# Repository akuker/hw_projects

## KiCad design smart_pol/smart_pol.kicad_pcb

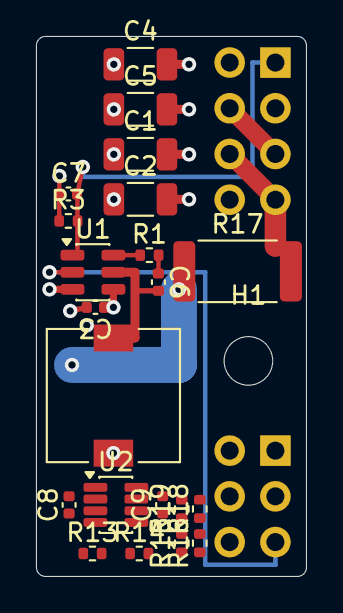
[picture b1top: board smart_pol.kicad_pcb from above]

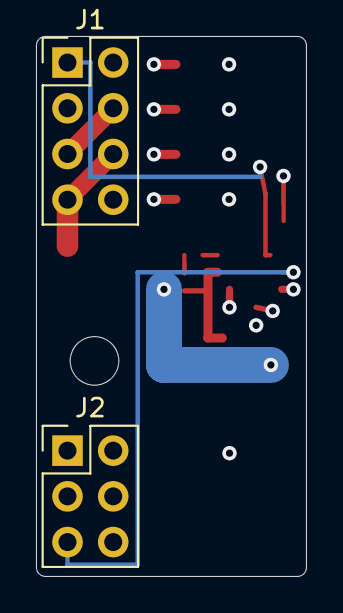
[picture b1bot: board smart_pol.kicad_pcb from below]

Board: 4 copper layers, 15.0 x 30.0 mm, 24 parts (2 on the bottom side), 16 nets.

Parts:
C1, C2: 10uF 50V; C_1206_3216Metric
C3, C6, C8, C9: 100nF; C_0402_1005Metric
C4, C5: 22uF 25V; C_1206_3216Metric
C7: 22pF; C_0402_1005Metric
H1: MountingHole; MountingHole_2.7mm_M2.5
J1: Power 2x4; PinHeader_2x04_P2.54mm_Vertical
J2: Logic 2x3; PinHeader_2x03_P2.54mm_Vertical
L1: 2.2uH 10A; L_7.3x7.3_H3.5
R1, R13, R14: 10R; R_0402_1005Metric
R3: 22k; R_0402_1005Metric
R15, R16: 4.7k; R_0402_1005Metric
R17: 10mR 2W; R_2512_6332Metric
R18, R19: 100k; R_0402_1005Metric
U1: ETA8156FT2G; SOT-23-6
U2: INA219AIDCNR; SOT-23-8

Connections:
ADDR0: J2.3, R19.1, U2.7 (A0)
ADDR1: J2.4, R18.1, U2.8 (A1)
EN: J2.5, U1.2 (EN)
FB: C7.2, J1.1, R3.2, U1.1 (FB)
GND: C1.2, C2.2, C3.2, C4.2, C5.2, C9.2, J1.2, J1.3, J1.8, R18.2, R19.2, U1.3 (GND), U2.3 (GND)
IN_M: C8.2, R14.2, U2.2 (IN-)
IN_P: C8.1, R13.2, U2.1 (IN+)
unnamed: C6.1, R1.2
unnamed: R1.1, U1.6 (BST)
unnamed: C6.2, L1.1, U1.5 (SW)
SCL: J2.2, R15.2, U2.5 (SCL)
SDA: J2.1, R16.2, U2.6 (SDA)
VBUCK: C4.1, C5.1, C7.1, L1.2, R3.1, R13.1, R17.1
VCC_IO: C9.1, J2.6, R15.1, R16.1, U2.4 (VS)
VIN: C1.1, C2.1, C3.1, J1.4, J1.5, U1.4 (IN)
VOUT: J1.6, J1.7, R14.1, R17.2

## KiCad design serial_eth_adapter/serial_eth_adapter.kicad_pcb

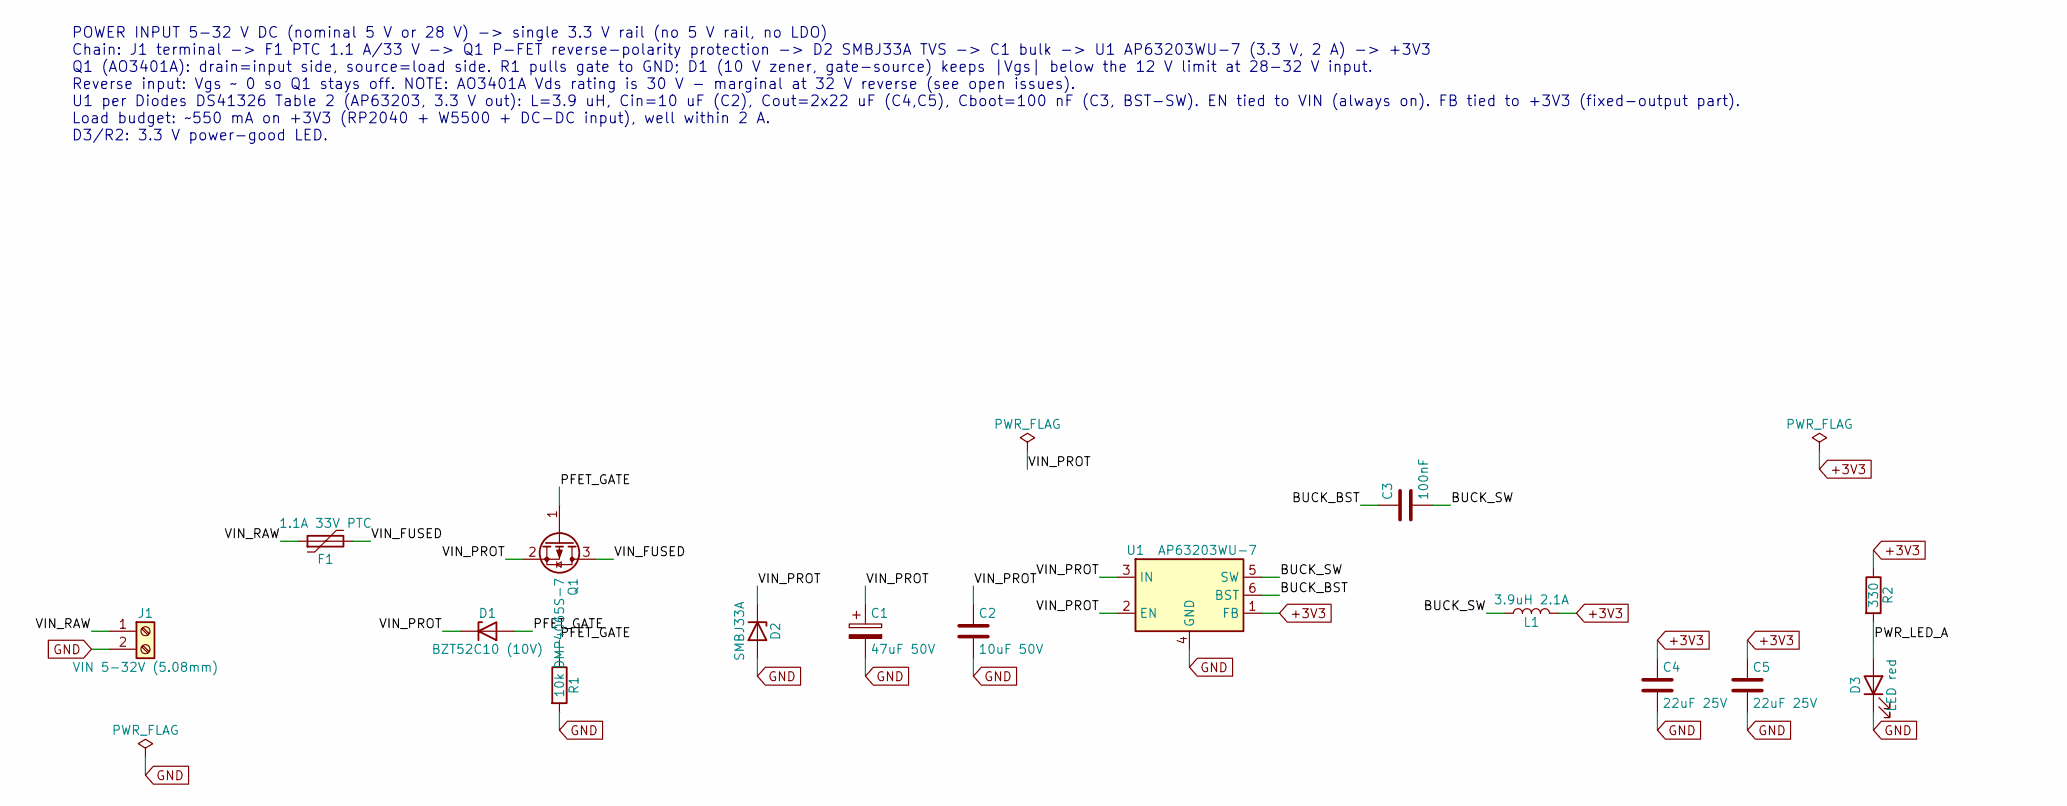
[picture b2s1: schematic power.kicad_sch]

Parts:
C1: 47uF 50V; CP_Elec_6.3x7.7; MPN RVT1H470M0607; LCSC C3349
C2: 10uF 50V; C_1206_3216Metric; MPN CL31A106KBHNNNE; LCSC C13585
C3: 100nF; C_0603_1608Metric; MPN CC0603KRX7R9BB104; LCSC C14663
C4, C5: 22uF 25V; C_0805_2012Metric; MPN CL21A226MAQNNNE; LCSC C45783
D1: BZT52C10 (10V); D_SOD-123; MPN BZT52C10; LCSC C2103
D2: SMBJ33A; D_SMB; MPN SMBJ33A; LCSC C173526
D3: LED red; LED_0603_1608Metric; MPN KT-0603R; LCSC C2286
F1: 1.1A 33V PTC; Fuse_1812_4532Metric; MPN 1812L110/33MR; LCSC C142747
J1: VIN 5-32V (5.08mm); PhoenixContact_MSTBA_2,5_2-G-5,08_1x02_P5.08mm_Horizontal; MPN KF2EDGR-5.08-2P; LCSC C441204
L1: 3.9uH 2.1A; L_Sunlord_SWPA4030S; MPN SWPA4030S3R9MT; LCSC C96899
Q1: DMP4065S-7; SOT-23; MPN DMP4065S-7; LCSC C182476
R1: 10k; R_0603_1608Metric; MPN 0603WAF1002T5E; LCSC C25804
R2: 330; R_0603_1608Metric; MPN 0603WAF3300T5E; LCSC C23138
U1: AP63203WU-7; TSOT-23-6; MPN AP63203WU-7; LCSC C780769

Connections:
+3V3: C4.1, C5.1, L1.2, R2.1, U1.1 (FB); also elsewhere on the board
/Power/BUCK_BST: C3.1, U1.6 (BST)
/Power/BUCK_SW: C3.2, L1.1, U1.5 (SW)
/Power/PFET_GATE: D1.2 (A), Q1.1 (G), R1.1
/Power/PWR_LED_A: D3.2 (A), R2.2
/Power/VIN_FUSED: F1.2, Q1.3 (D)
/Power/VIN_PROT: C1.1, C2.1, D1.1 (K), D2.1 (K), Q1.2 (S), U1.2 (EN), U1.3 (IN)
/Power/VIN_RAW: F1.1, J1.1
GND: C1.2, C2.2, C4.2, C5.2, D2.2 (A), D3.1 (K), J1.2, R1.2, U1.4 (GND); also elsewhere on the board

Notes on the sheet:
POWER INPUT 5-32 V DC (nominal 5 V or 28 V) -> single 3.3 V rail (no 5 V rail, no LDO) Chain: J1 terminal -> F1 PTC 1.1 A/33 V -> Q1 P-FET reverse-polarity protection -> D2 SMBJ33A TVS -> C1 bulk -> U1 AP63203WU-7 (3.3 V, 2 A) -> +3V3 Q1 (AO3401A): drain=input side, source=load side. R1 pulls gate 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

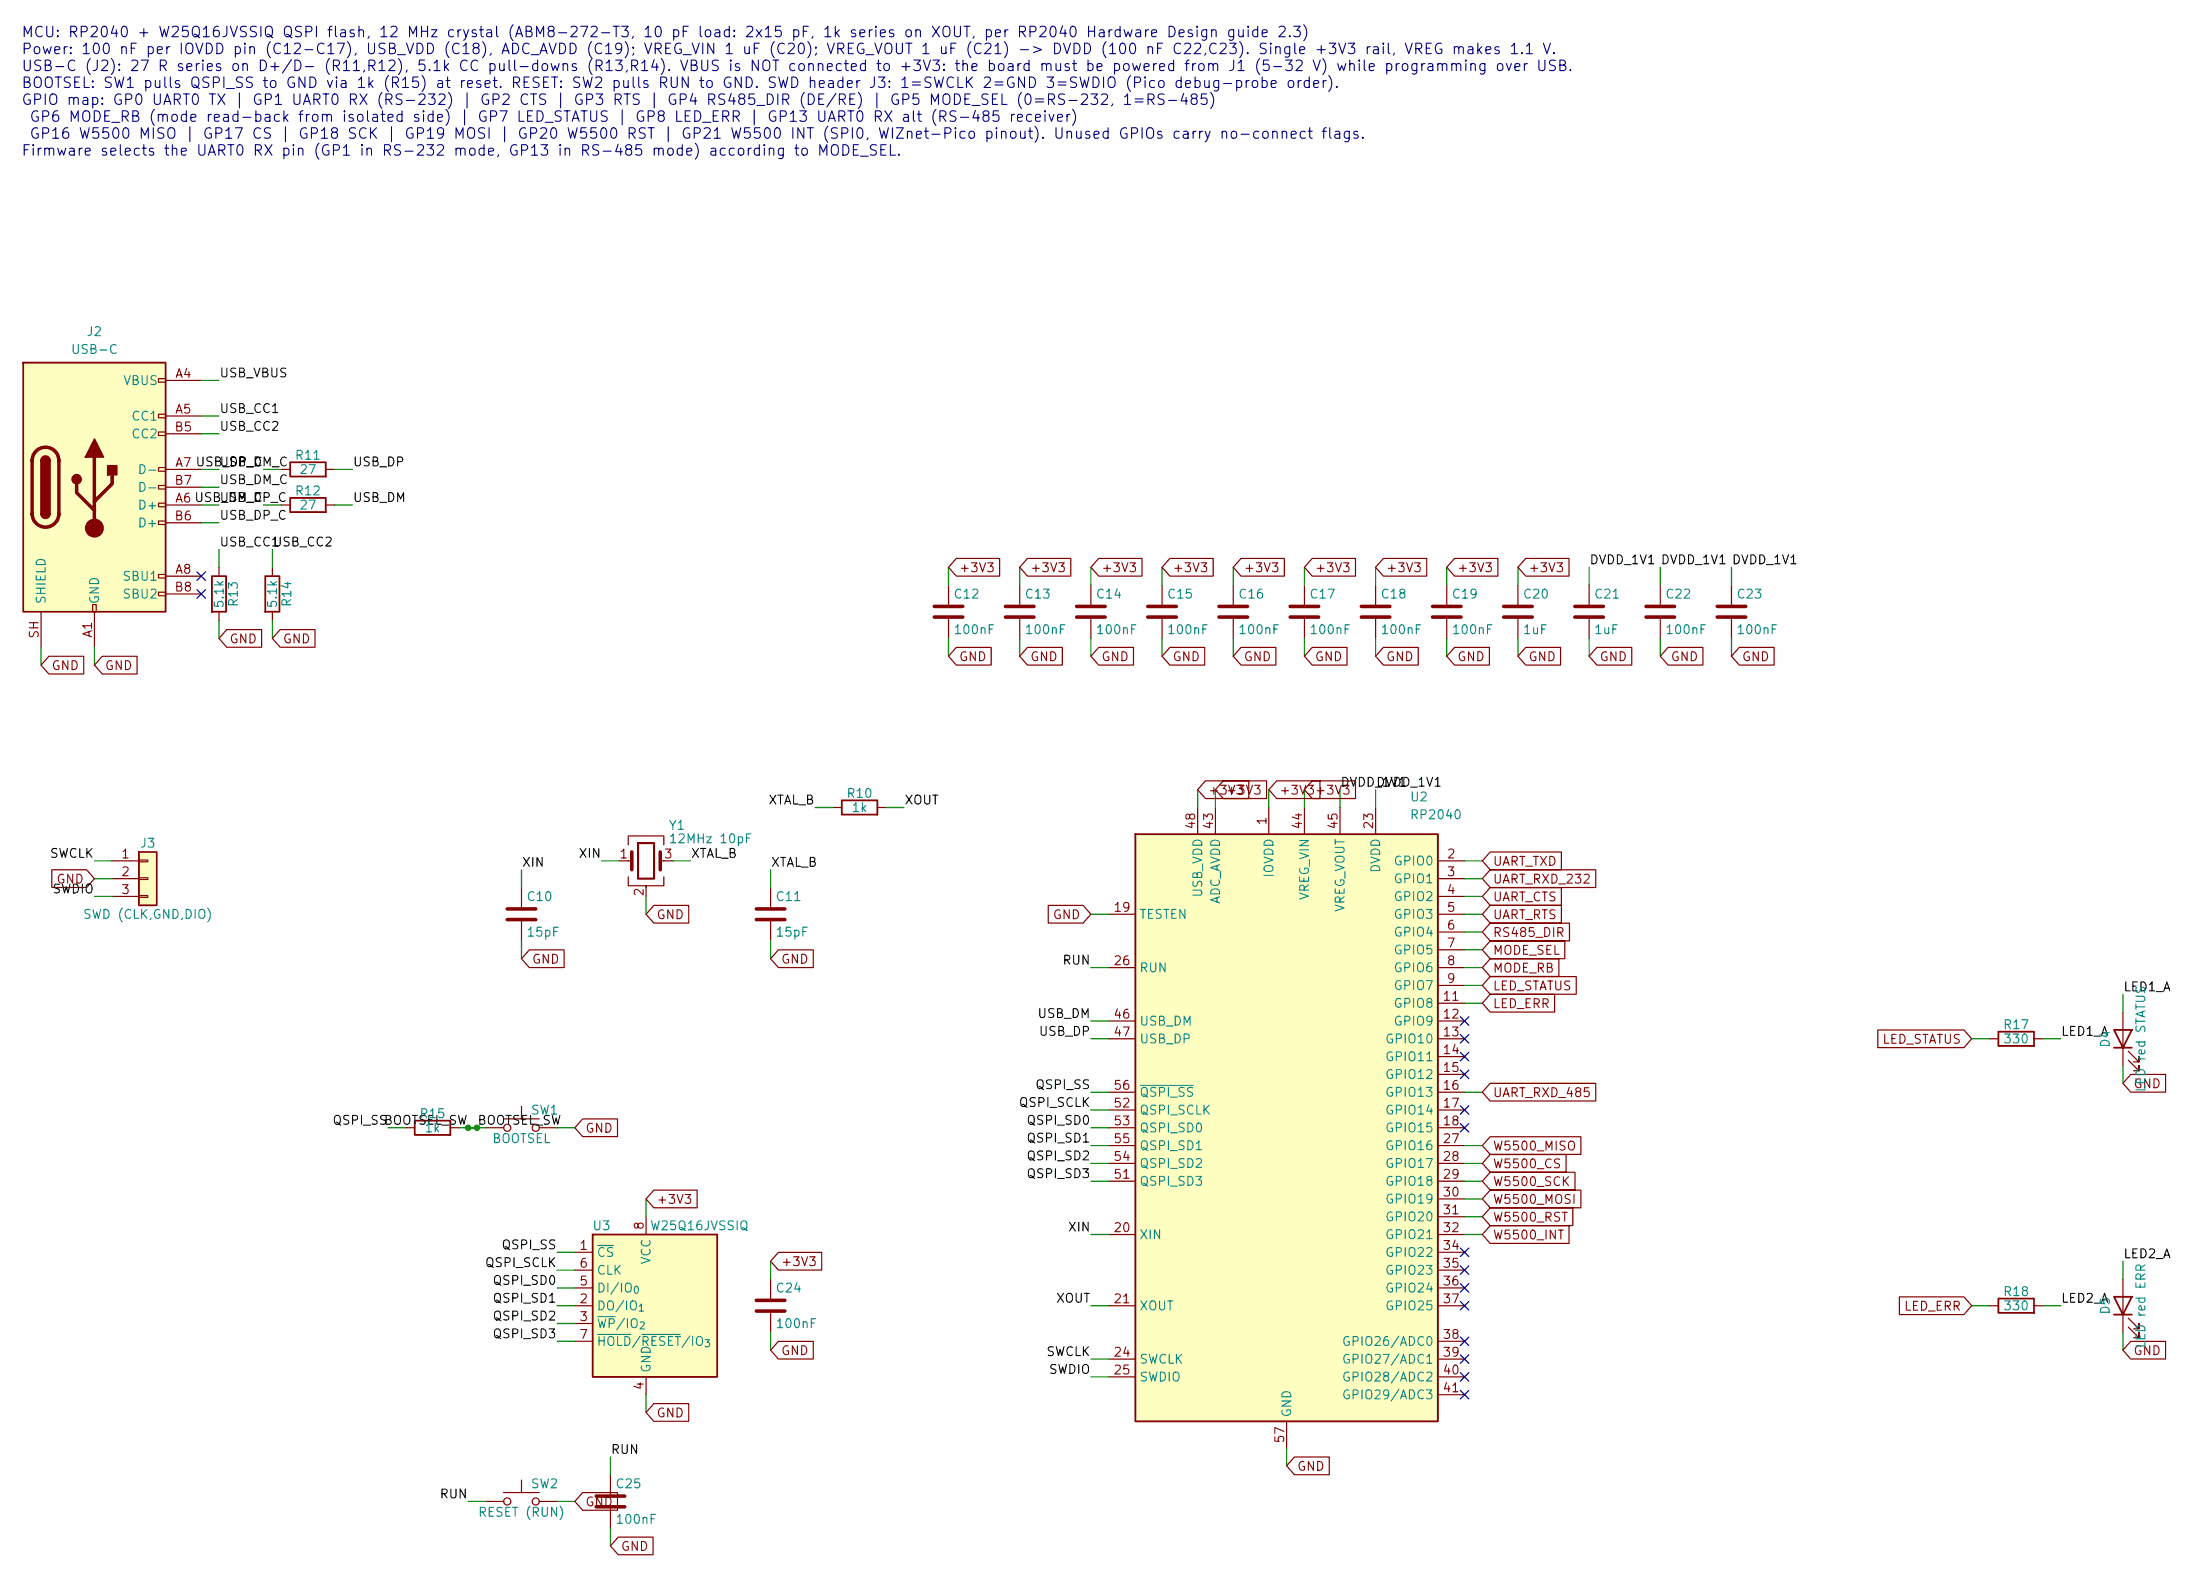
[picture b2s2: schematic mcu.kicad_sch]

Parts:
C10, C11: 15pF; C_0603_1608Metric; MPN CL10C150JB8NNNC; LCSC C1644
C12, C13, C14, C15, C16, C17, C18, C19, C22, C23, C24, C25: 100nF; C_0603_1608Metric; MPN CC0603KRX7R9BB104; LCSC C14663
C20, C21: 1uF; C_0603_1608Metric; MPN CL10A105KB8NNNC; LCSC C15849
D4: LED red STATUS; LED_0603_1608Metric; MPN KT-0603R; LCSC C2286
D5: LED red ERR; LED_0603_1608Metric; MPN KT-0603R; LCSC C2286
J2: USB-C; USB_C_Receptacle_HRO_TYPE-C-31-M-12; MPN TYPE-C-31-M-12; LCSC C165948
J3: SWD (CLK,GND,DIO); PinHeader_1x03_P2.54mm_Vertical; MPN 254PZ-1x3P-V; LCSC C53055673
R10, R15: 1k; R_0603_1608Metric; MPN 0603WAF1001T5E; LCSC C21190
R11, R12: 27; R_0603_1608Metric; MPN 0603WAF270JT5E; LCSC C25190
R13, R14: 5.1k; R_0603_1608Metric; MPN 0603WAF5101T5E; LCSC C23186
R17, R18: 330; R_0603_1608Metric; MPN 0603WAF3300T5E; LCSC C23138
SW1: BOOTSEL; SW_TS-1187A_5.1x5.1mm; MPN TS-1187A-B-A-B; LCSC C318884
SW2: RESET (RUN); SW_TS-1187A_5.1x5.1mm; MPN TS-1187A-B-A-B; LCSC C318884
U2: RP2040; QFN-56-1EP_7x7mm_P0.4mm_EP3.2x3.2mm; MPN RP2040; LCSC C2040
U3: W25Q16JVSSIQ; SOIC-8_5.3x5.3mm_P1.27mm; MPN W25Q16JVSSIQ; LCSC C82317
Y1: 12MHz 10pF; Crystal_SMD_3225-4Pin_3.2x2.5mm; MPN ABM8-272-T3; LCSC C20625731

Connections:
+3V3: C12.1, C13.1, C14.1, C15.1, C16.1, C17.1, C18.1, C19.1, C20.1, C24.1, U2.1 (IOVDD), U2.10 (IOVDD), U2.22 (IOVDD), U2.33 (IOVDD), U2.42 (IOVDD), U2.43 (ADC_AVDD), U2.44 (VREG_VIN), U2.48 (USB_VDD), U2.49 (IOVDD), U3.8 (VCC); also elsewhere on the board
/MCU/BOOTSEL_SW: R15.2, SW1.1
/MCU/DVDD_1V1: C21.1, C22.1, C23.1, U2.23 (DVDD), U2.45 (VREG_VOUT), U2.50 (DVDD)
/MCU/LED1_A: D4.2 (A), R17.2
/MCU/LED2_A: D5.2 (A), R18.2
/MCU/QSPI_SCLK: U2.52 (QSPI_SCLK), U3.6 (CLK)
/MCU/QSPI_SD0: U2.53 (QSPI_SD0), U3.5 (DI/IO_{0})
/MCU/QSPI_SD1: U2.55 (QSPI_SD1), U3.2 (DO/IO_{1})
/MCU/QSPI_SD2: U2.54 (QSPI_SD2), U3.3 (~WP/IO_{2})
/MCU/QSPI_SD3: U2.51 (QSPI_SD3), U3.7 (~HOLD/~RESET/IO_{3})
/MCU/QSPI_SS: R15.1, U2.56 (~QSPI_SS), U3.1 (~CS)
/MCU/RUN: C25.1, SW2.1, U2.26 (RUN)
/MCU/SWCLK: J3.1, U2.24 (SWCLK)
/MCU/SWDIO: J3.3, U2.25 (SWDIO)
/MCU/USB_CC1: J2.A5 (CC1), R13.1
/MCU/USB_CC2: J2.B5 (CC2), R14.1
/MCU/USB_DM: R12.2, U2.46 (USB_DM)
/MCU/USB_DM_C: J2.A7 (D-), J2.B7 (D-), R12.1
/MCU/USB_DP: R11.2, U2.47 (USB_DP)
/MCU/USB_DP_C: J2.A6 (D+), J2.B6 (D+), R11.1
/MCU/USB_VBUS: J2.A4 (VBUS), J2.A9 (VBUS), J2.B4 (VBUS), J2.B9 (VBUS)
/MCU/XIN: C10.1, U2.20 (XIN), Y1.1
/MCU/XOUT: R10.2, U2.21 (XOUT)
/MCU/XTAL_B: C11.1, R10.1, Y1.3
GND: C10.2, C11.2, C12.2, C13.2, C14.2, C15.2, C16.2, C17.2, C18.2, C19.2, C20.2, C21.2, C22.2, C23.2, C24.2, C25.2, D4.1 (K), D5.1 (K), J2.A1 (GND), J2.A12 (GND), J2.B1 (GND), J2.B12 (GND), J2.SH (SHIELD), J3.2, R13.2, R14.2, SW1.2, SW2.2, U2.19 (TESTEN), U2.57 (GND), U3.4 (GND), Y1.2 (G), Y1.4 (G); also elsewhere on the board
LED_ERR: R18.1, U2.11 (GPIO8)
LED_STATUS: R17.1, U2.9 (GPIO7)
MODE_RB: U2.8 (GPIO6); also elsewhere on the board
MODE_SEL: U2.7 (GPIO5); also elsewhere on the board
RS485_DIR: U2.6 (GPIO4); also elsewhere on the board
UART_CTS: U2.4 (GPIO2); also elsewhere on the board
UART_RTS: U2.5 (GPIO3); also elsewhere on the board
UART_RXD_232: U2.3 (GPIO1); also elsewhere on the board
UART_RXD_485: U2.16 (GPIO13); also elsewhere on the board
UART_TXD: U2.2 (GPIO0); also elsewhere on the board
W5500_CS: U2.28 (GPIO17); also elsewhere on the board
W5500_INT: U2.32 (GPIO21); also elsewhere on the board
W5500_MISO: U2.27 (GPIO16); also elsewhere on the board
W5500_MOSI: U2.30 (GPIO19); also elsewhere on the board
W5500_RST: U2.31 (GPIO20); also elsewhere on the board
W5500_SCK: U2.29 (GPIO18); also elsewhere on the board

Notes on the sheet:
MCU: RP2040 + W25Q16JVSSIQ QSPI flash, 12 MHz crystal (ABM8-272-T3, 10 pF load: 2x15 pF, 1k series on XOUT, per RP2040 Hardware Design guide 2.3) Power: 100 nF per IOVDD pin (C12-C17), USB_VDD (C18), ADC_AVDD (C19); VREG_VIN 1 uF (C20); VREG_VOUT 1 uF (C21) -> DVDD (100 nF C22,C23). Single +3V3 rai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

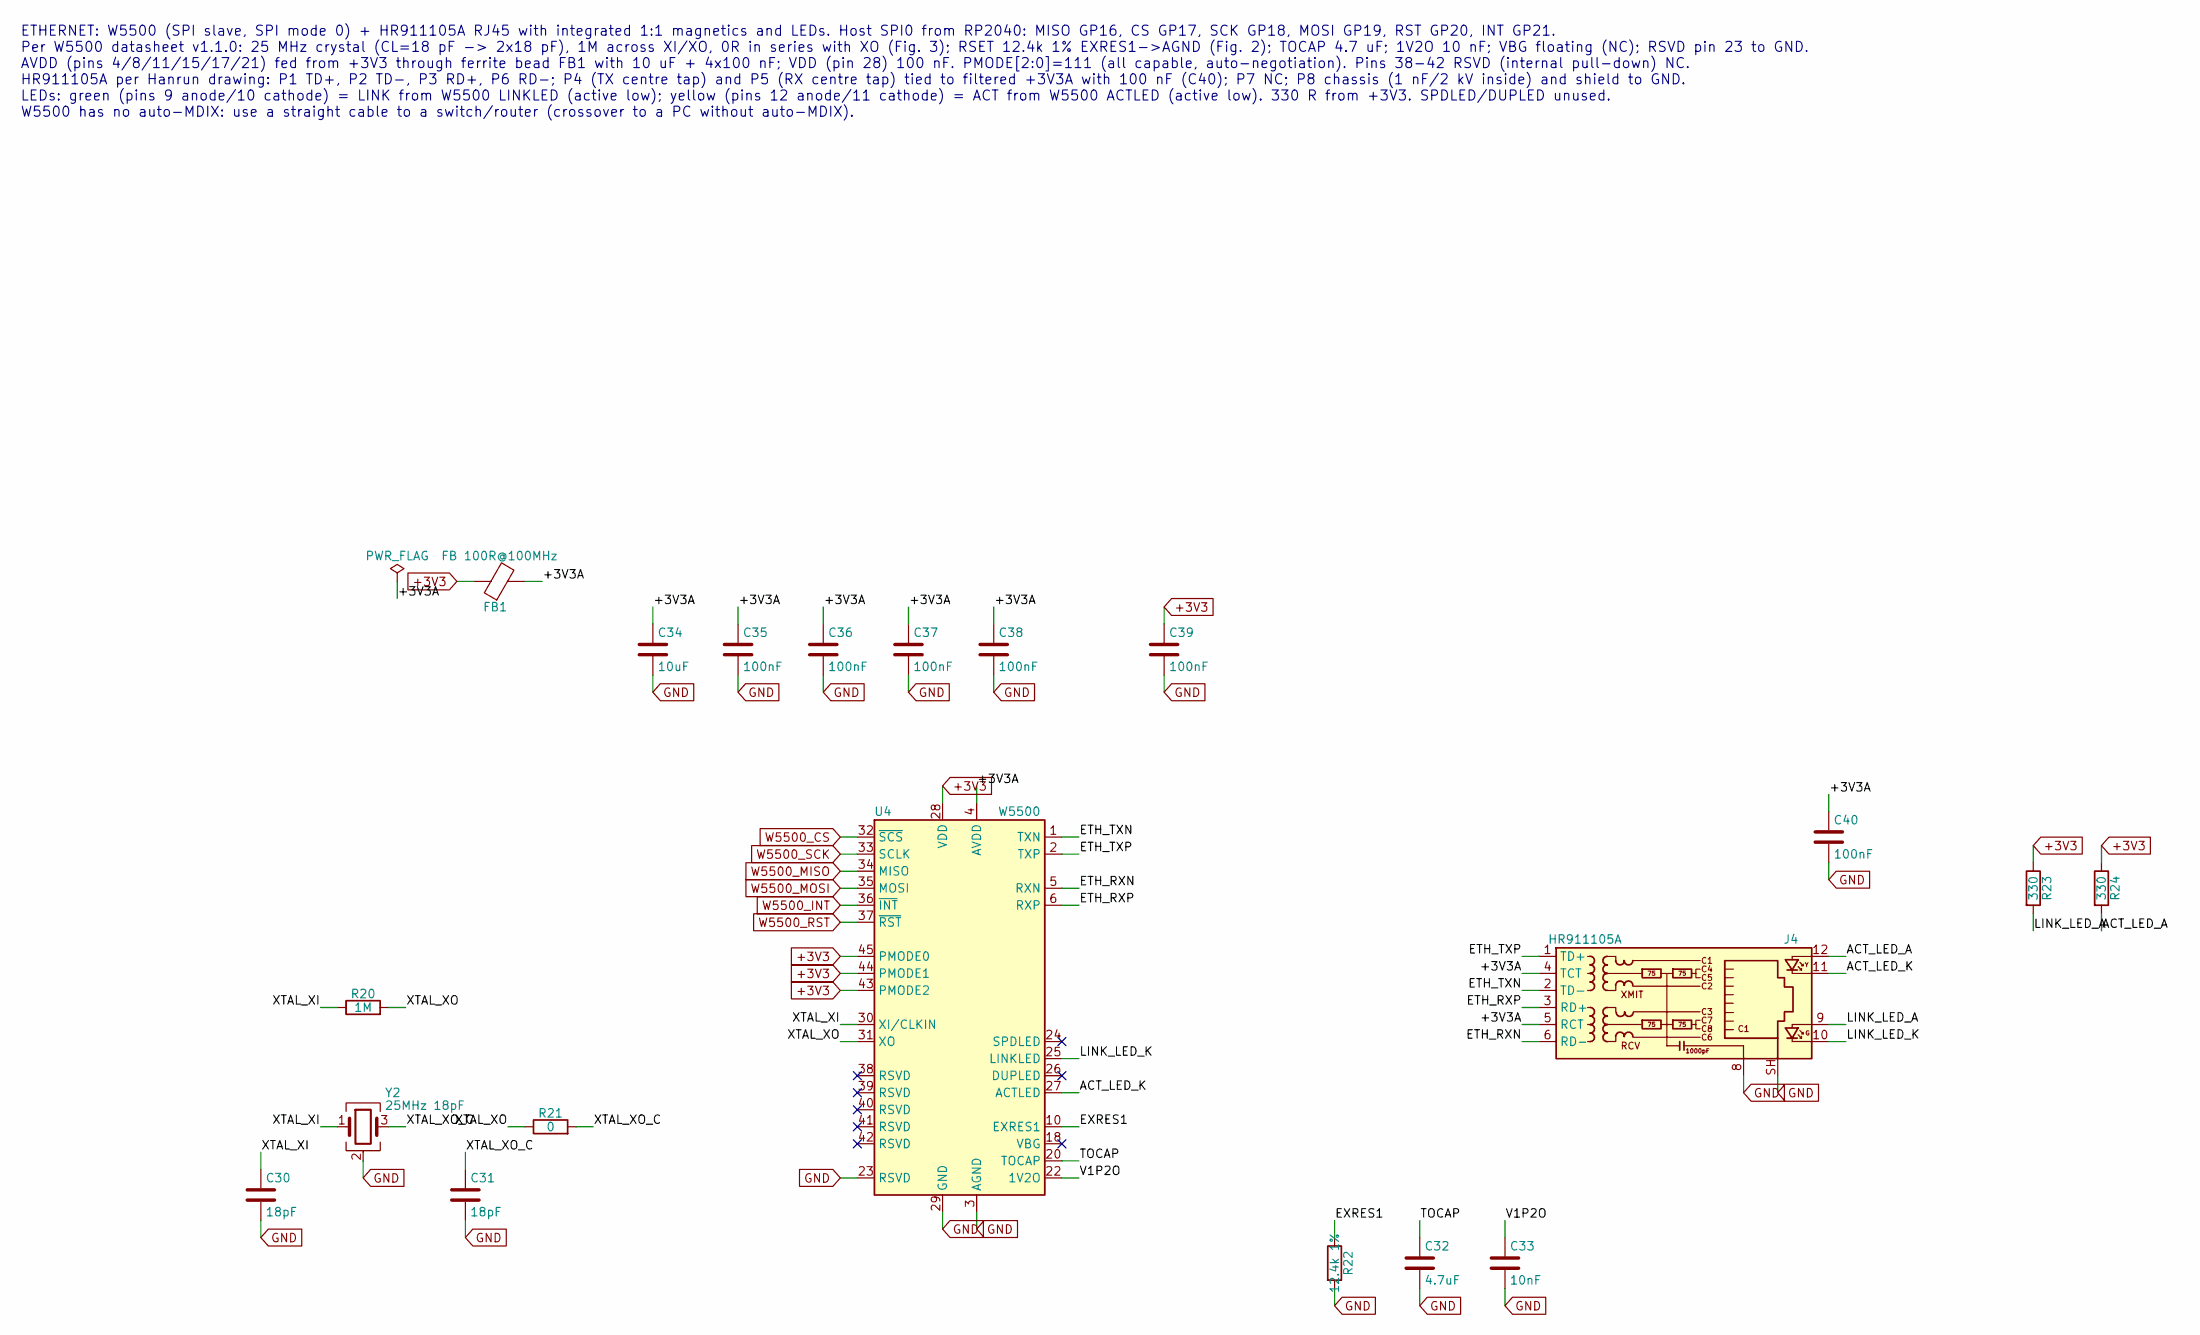
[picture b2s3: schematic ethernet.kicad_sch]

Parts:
C30, C31: 18pF; C_0603_1608Metric; MPN CL10C180JB8NNNC; LCSC C1647
C32: 4.7uF; C_0603_1608Metric; MPN CL10A475KO8NNNC; LCSC C19666
C33: 10nF; C_0603_1608Metric; MPN 0603B103K500NT; LCSC C57112
C34: 10uF; C_0603_1608Metric; MPN CL10A106KP8NNNC; LCSC C19702
C35, C36, C37, C38, C39, C40: 100nF; C_0603_1608Metric; MPN CC0603KRX7R9BB104; LCSC C14663
FB1: FB 100R@100MHz; L_0805_2012Metric; MPN GZ2012D101TF; LCSC C1015
J4: HR911105A; RJ45_Hanrun_HR911105A_Horizontal; MPN HR911105A; LCSC C12074
R20: 1M; R_0603_1608Metric; MPN 0603WAF1004T5E; LCSC C22935
R21: 0; R_0603_1608Metric; MPN 0603WAF0000T5E; LCSC C21189
R22: 12.4k 1%; R_0603_1608Metric; MPN 0603WAF1242T5E; LCSC C22865
R23, R24: 330; R_0603_1608Metric; MPN 0603WAF3300T5E; LCSC C23138
U4: W5500; LQFP-48_7x7mm_P0.5mm; MPN W5500; LCSC C32843
Y2: 25MHz 18pF; Crystal_SMD_3225-4Pin_3.2x2.5mm; MPN ABM8-25.000MHZ-D2Y-T; LCSC C179643

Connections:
+3V3: C39.1, FB1.1, R23.1, R24.1, U4.28 (VDD), U4.43 (PMODE2), U4.44 (PMODE1), U4.45 (PMODE0); also elsewhere on the board
/Ethernet/+3V3A: C34.1, C35.1, C36.1, C37.1, C38.1, C40.1, FB1.2, J4.4 (TCT), J4.5 (RCT), U4.4 (AVDD), U4.8 (AVDD), U4.11 (AVDD), U4.15 (AVDD), U4.17 (AVDD), U4.21 (AVDD)
/Ethernet/ACT_LED_A: J4.12, R24.2
/Ethernet/ACT_LED_K: J4.11, U4.27 (ACTLED)
/Ethernet/ETH_RXN: J4.6 (RD-), U4.5 (RXN)
/Ethernet/ETH_RXP: J4.3 (RD+), U4.6 (RXP)
/Ethernet/ETH_TXN: J4.2 (TD-), U4.1 (TXN)
/Ethernet/ETH_TXP: J4.1 (TD+), U4.2 (TXP)
/Ethernet/EXRES1: R22.1, U4.10 (EXRES1)
/Ethernet/LINK_LED_A: J4.9, R23.2
/Ethernet/LINK_LED_K: J4.10, U4.25 (LINKLED)
/Ethernet/TOCAP: C32.1, U4.20 (TOCAP)
/Ethernet/V1P2O: C33.1, U4.22 (1V2O)
/Ethernet/XTAL_XI: C30.1, R20.1, U4.30 (XI/CLKIN), Y2.1
/Ethernet/XTAL_XO: R20.2, R21.1, U4.31 (XO)
/Ethernet/XTAL_XO_C: C31.1, R21.2, Y2.3
GND: C30.2, C31.2, C32.2, C33.2, C34.2, C35.2, C36.2, C37.2, C38.2, C39.2, C40.2, J4.8, J4.SH, R22.2, U4.3 (AGND), U4.9 (AGND), U4.14 (AGND), U4.16 (AGND), U4.19 (AGND), U4.23 (RSVD), U4.29 (GND), U4.48 (AGND), Y2.2 (G), Y2.4 (G); also elsewhere on the board
W5500_CS: U4.32 (~SCS); also elsewhere on the board
W5500_INT: U4.36 (~INT); also elsewhere on the board
W5500_MISO: U4.34 (MISO); also elsewhere on the board
W5500_MOSI: U4.35 (MOSI); also elsewhere on the board
W5500_RST: U4.37 (~RST); also elsewhere on the board
W5500_SCK: U4.33 (SCLK); also elsewhere on the board

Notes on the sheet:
ETHERNET: W5500 (SPI slave, SPI mode 0) + HR911105A RJ45 with integrated 1:1 magnetics and LEDs. Host SPI0 from RP2040: MISO GP16, CS GP17, SCK GP18, MOSI GP19, RST GP20, INT GP21. Per W5500 datasheet v1.1.0: 25 MHz crystal (CL=18 pF -> 2x18 pF), 1M across XI/XO, 0R in series with XO (Fig. 3); RSET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

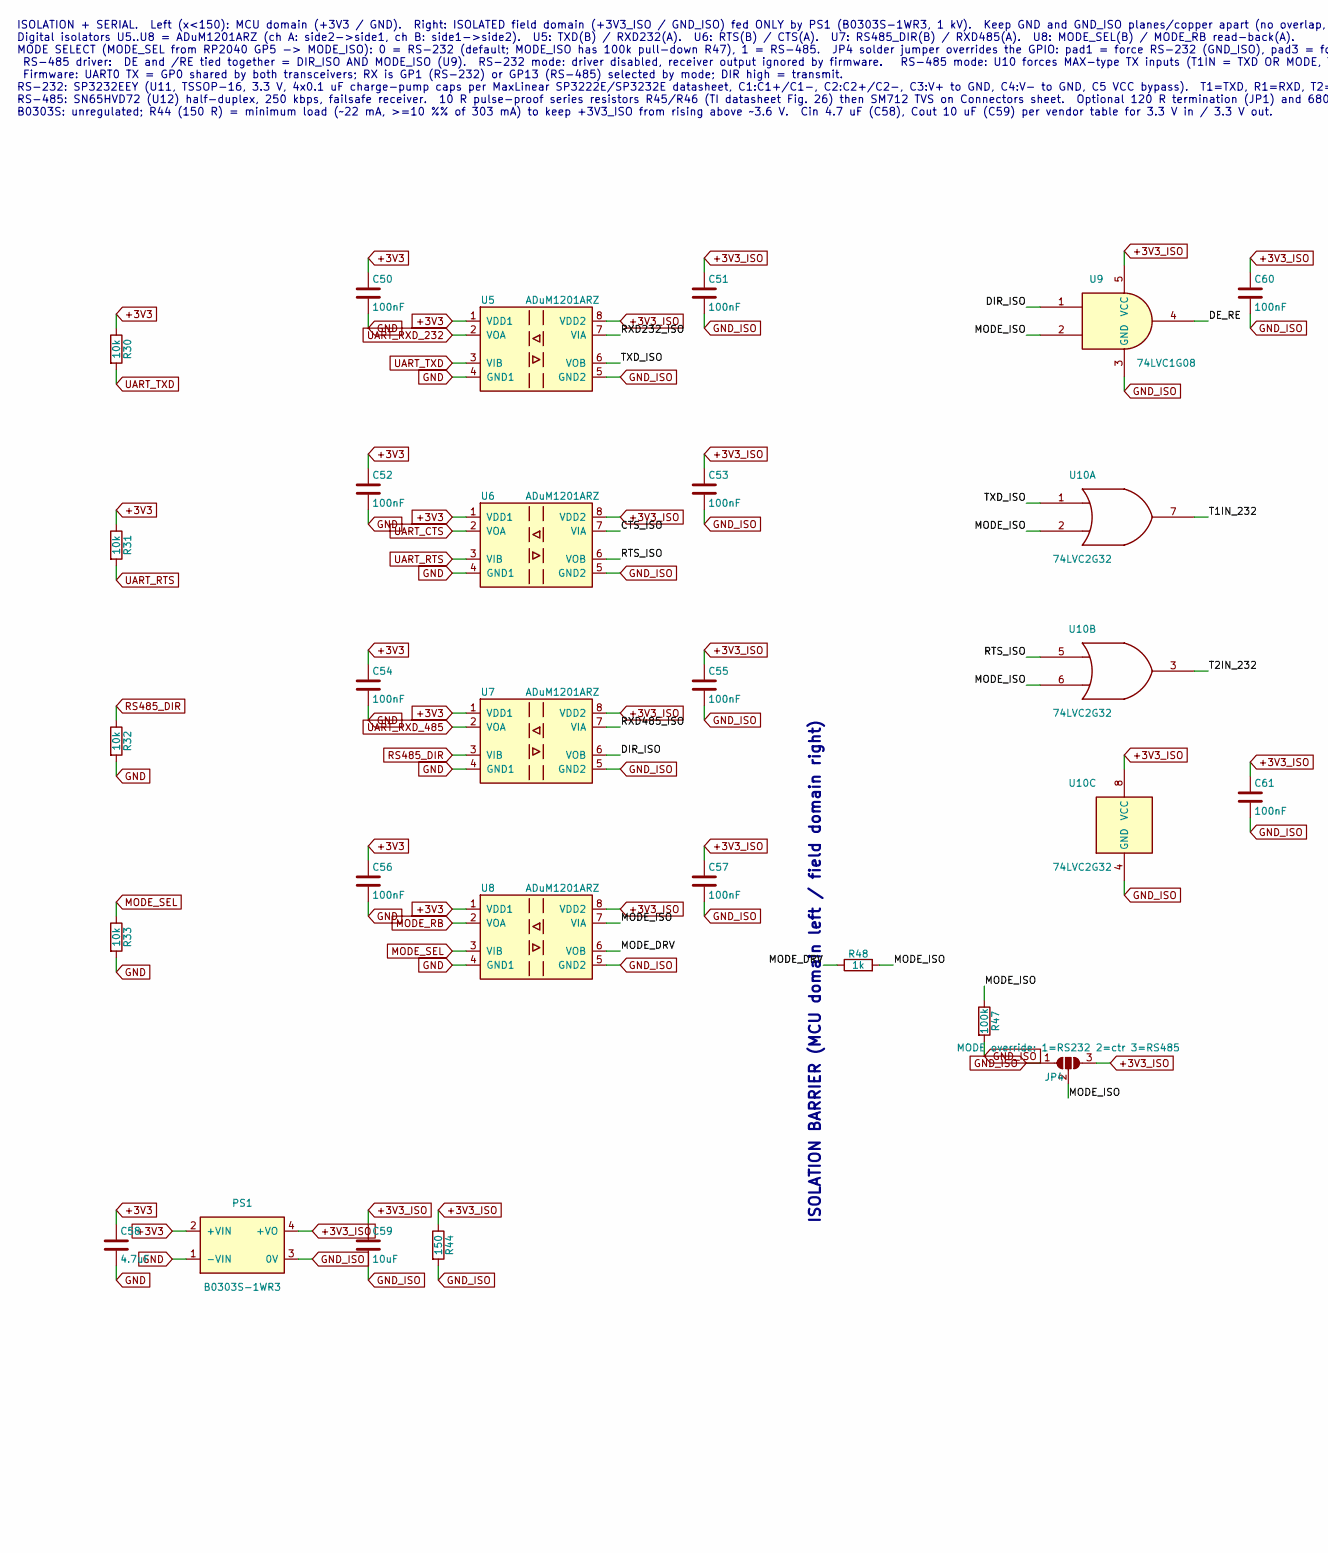
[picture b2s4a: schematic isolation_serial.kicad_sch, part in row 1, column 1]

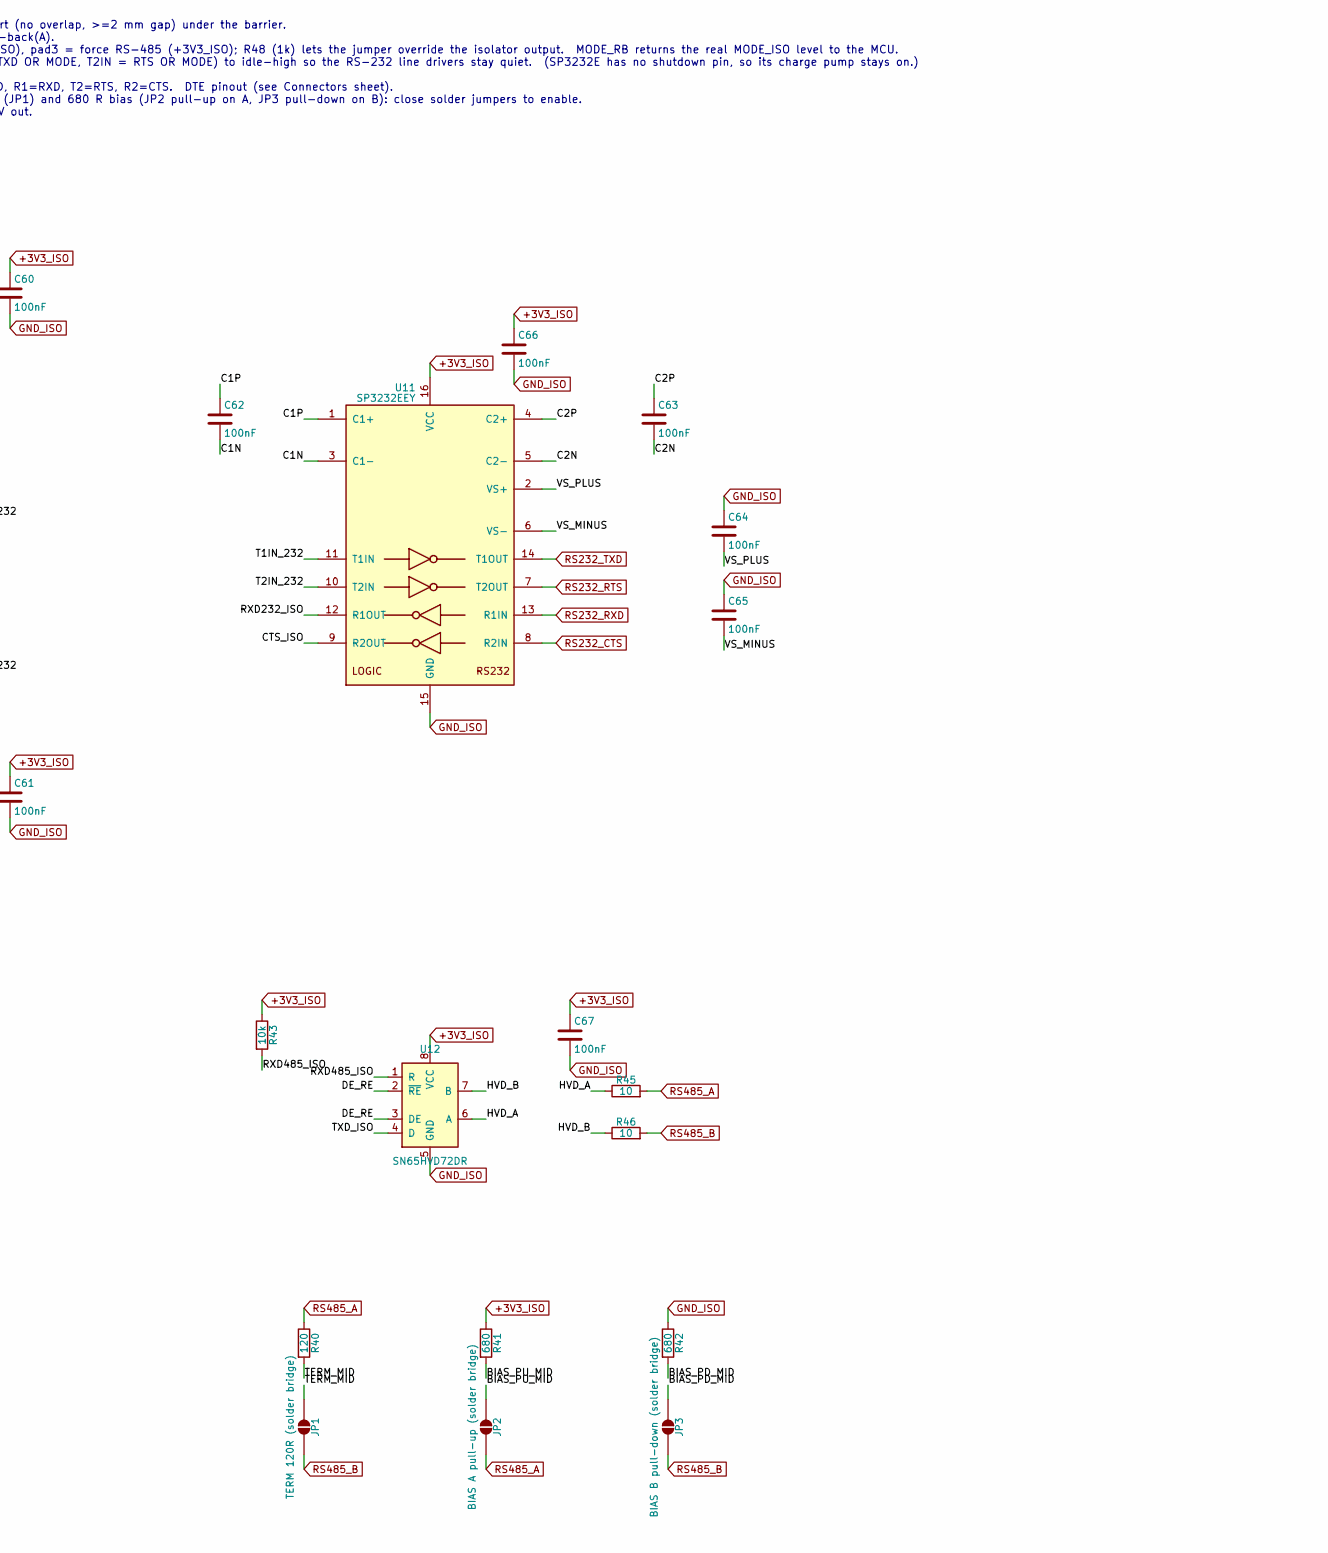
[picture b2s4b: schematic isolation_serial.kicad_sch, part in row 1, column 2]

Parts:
C50, C51, C52, C53, C54, C55, C56, C57, C60, C61, C62, C63, C64, C65, C66, C67: 100nF; C_0603_1608Metric; MPN CC0603KRX7R9BB104; LCSC C14663
C58: 4.7uF; C_0603_1608Metric; MPN CL10A475KO8NNNC; LCSC C19666
C59: 10uF; C_0603_1608Metric; MPN CL10A106KP8NNNC; LCSC C19702
JP1: TERM 120R (solder bridge); SolderJumper-2_P1.3mm_Open_Pad1.0x1.5mm; LCSC N/A (PCB pads)
JP2: BIAS A pull-up (solder bridge); SolderJumper-2_P1.3mm_Open_Pad1.0x1.5mm; LCSC N/A (PCB pads)
JP3: BIAS B pull-down (solder bridge); SolderJumper-2_P1.3mm_Open_Pad1.0x1.5mm; LCSC N/A (PCB pads)
JP4: MODE override: 1=RS232 2=ctr 3=RS485; SolderJumper-3_P1.3mm_Open_Pad1.0x1.5mm_NumberLabels; LCSC N/A (PCB pads)
PS1: B0303S-1WR3; SIP-4_B0303S-1WR3_11.6x6mm_P2.54mm; MPN B0303S-1WR3; LCSC C7465185
R30, R31, R32, R33, R43: 10k; R_0603_1608Metric; MPN 0603WAF1002T5E; LCSC C25804
R40: 120; R_0603_1608Metric; MPN 0603WAF1200T5E; LCSC C22787
R41, R42: 680; R_0603_1608Metric; MPN 0603WAF6800T5E; LCSC C23228
R44: 150; R_0603_1608Metric; MPN 0603WAF1500T5E; LCSC C22808
R45, R46: 10; R_0603_1608Metric; MPN 0603WAF100JT5E; LCSC C22859
R47: 100k; R_0603_1608Metric; MPN 0603WAF1003T5E; LCSC C25803
R48: 1k; R_0603_1608Metric; MPN 0603WAF1001T5E; LCSC C21190
U5, U6, U7, U8: ADuM1201ARZ; SOIC-8_3.9x4.9mm_P1.27mm; MPN ADUM1201ARZ-RL7; LCSC C9669
U9: 74LVC1G08; SOT-23-5; MPN SN74LVC1G08DBVR; LCSC C7666
U10: 74LVC2G32; VSSOP-8_2.3x2mm_P0.5mm; MPN SN74LVC2G32DCUR; LCSC C91874
U11: SP3232EEY; TSSOP-16_4.4x5mm_P0.65mm; MPN SP3232EEY-L/TR; LCSC C13482
U12: SN65HVD72DR; SOIC-8_3.9x4.9mm_P1.27mm; MPN SN65HVD72DR; LCSC C48125

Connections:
+3V3: C50.1, C52.1, C54.1, C56.1, C58.1, PS1.2 (+VIN), R30.1, R31.1, U5.1 (VDD1), U6.1 (VDD1), U7.1 (VDD1), U8.1 (VDD1); also elsewhere on the board
+3V3_ISO: C51.1, C53.1, C55.1, C57.1, C59.1, C60.1, C61.1, C66.1, C67.1, JP4.3 (B), PS1.4 (+VO), R41.1, R43.1, R44.1, U5.8 (VDD2), U6.8 (VDD2), U7.8 (VDD2), U8.8 (VDD2), U9.5 (VCC), U10.8 (VCC), U11.16 (VCC), U12.8 (VCC)
/Isolation + Serial/BIAS_PD_MID: JP3.1 (A), R42.2
/Isolation + Serial/BIAS_PU_MID: JP2.1 (A), R41.2
/Isolation + Serial/C1N: C62.2, U11.3 (C1-)
/Isolation + Serial/C1P: C62.1, U11.1 (C1+)
/Isolation + Serial/C2N: C63.2, U11.5 (C2-)
/Isolation + Serial/C2P: C63.1, U11.4 (C2+)
/Isolation + Serial/CTS_ISO: U6.7 (VIA), U11.9 (R2OUT)
/Isolation + Serial/DE_RE: U9.4, U12.2 (~RE), U12.3 (DE)
/Isolation + Serial/DIR_ISO: U7.6 (VOB), U9.1
/Isolation + Serial/HVD_A: R45.1, U12.6 (A)
/Isolation + Serial/HVD_B: R46.1, U12.7 (B)
/Isolation + Serial/MODE_DRV: R48.1, U8.6 (VOB)
/Isolation + Serial/MODE_ISO: JP4.2 (C), R47.1, R48.2, U8.7 (VIA), U9.2, U10.2, U10.6
/Isolation + Serial/RTS_ISO: U6.6 (VOB), U10.5
/Isolation + Serial/RXD232_ISO: U5.7 (VIA), U11.12 (R1OUT)
/Isolation + Serial/RXD485_ISO: R43.2, U7.7 (VIA), U12.1 (R)
/Isolation + Serial/T1IN_232: U10.7, U11.11 (T1IN)
/Isolation + Serial/T2IN_232: U10.3, U11.10 (T2IN)
/Isolation + Serial/TERM_MID: JP1.1 (A), R40.2
/Isolation + Serial/TXD_ISO: U5.6 (VOB), U10.1, U12.4 (D)
/Isolation + Serial/VS_MINUS: C65.2, U11.6 (VS-)
/Isolation + Serial/VS_PLUS: C64.2, U11.2 (VS+)
GND: C50.2, C52.2, C54.2, C56.2, C58.2, PS1.1 (-VIN), R32.2, R33.2, U5.4 (GND1), U6.4 (GND1), U7.4 (GND1), U8.4 (GND1); also elsewhere on the board
GND_ISO: C51.2, C53.2, C55.2, C57.2, C59.2, C60.2, C61.2, C64.1, C65.1, C66.2, C67.2, JP4.1 (A), PS1.3 (0V), R42.1, R44.2, R47.2, U5.5 (GND2), U6.5 (GND2), U7.5 (GND2), U8.5 (GND2), U9.3 (GND), U10.4 (GND), U11.15 (GND), U12.5 (GND); also elsewhere on the board
MODE_RB: U8.2 (VOA); also elsewhere on the board
MODE_SEL: R33.1, U8.3 (VIB); also elsewhere on the board
RS232_CTS: U11.8 (R2IN); also elsewhere on the board
RS232_RTS: U11.7 (T2OUT); also elsewhere on the board
RS232_RXD: U11.13 (R1IN); also elsewhere on the board
RS232_TXD: U11.14 (T1OUT); also elsewhere on the board
RS485_A: JP2.2 (B), R40.1, R45.2; also elsewhere on the board
RS485_B: JP1.2 (B), JP3.2 (B), R46.2; also elsewhere on the board
RS485_DIR: R32.1, U7.3 (VIB); also elsewhere on the board
UART_CTS: U6.2 (VOA); also elsewhere on the board
UART_RTS: R31.2, U6.3 (VIB); also elsewhere on the board
UART_RXD_232: U5.2 (VOA); also elsewhere on the board
UART_RXD_485: U7.2 (VOA); also elsewhere on the board
UART_TXD: R30.2, U5.3 (VIB); also elsewhere on the board

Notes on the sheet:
ISOLATION + SERIAL. Left (x<150): MCU domain (+3V3 / GND). Right: ISOLATED field domain (+3V3_ISO / GND_ISO) fed ONLY by PS1 (B0303S-1WR3, 1 kV). Keep GND and GND_ISO planes/copper apart (no overlap, >=2 mm gap) under the barrier. Digital isolators U5..U8 = ADuM1201ARZ (ch A: side2->side1, ch B: si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
ISOLATION BARRIER (MCU domain left / field domain right)

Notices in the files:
Power_Relay_Pico/Power_Relay_Pico.kicad_pcb:
(c)2025 akuker
fifty_pin_header_breakout/fifty_pin_header_breakout.kicad_pcb:
Copyright (c) 2024 akuker
pixel_grid/pixel_grid.kicad_pcb:
(c) 2024 akuker
